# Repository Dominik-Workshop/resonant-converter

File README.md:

# Resonant Converter

## Overview

This project is an LLC resonant converter. The power supply is designed to step down a nominal 60V input to a 12V output, capable of delivering up to 10A of continuous current (120W).

The board features power telemetry using an INA219 sensor, which can be easily interfaced via a standard QWIIC connector.

### Key Features

* **Input Voltage:** 60V ± 5%
* **Output:** 12V @ 10A
* **Topology:** LLC Resonant Converter
* **Telemetry:** Onboard INA219 power monitor with a QWIIC I2C connector
* **Magnetics:** Custom-wound transformer

## Project Status

**Design:** ✅ → **Fabrication & Assembly:** ✅ → **Bring-up:** ✅

> [!IMPORTANT]
> **Hardware modification required (rev.1.0.0):**
>
> Replace `R20` with a diode (e.g. `1N4148`) to prevent VCCP from backfeeding `U3`. Without this fix, VCCP remains too low for the LLC controller `U1` to start up.

## Used Tools

* [KiCad](https://www.kicad.org/) - Schematic and PCB design

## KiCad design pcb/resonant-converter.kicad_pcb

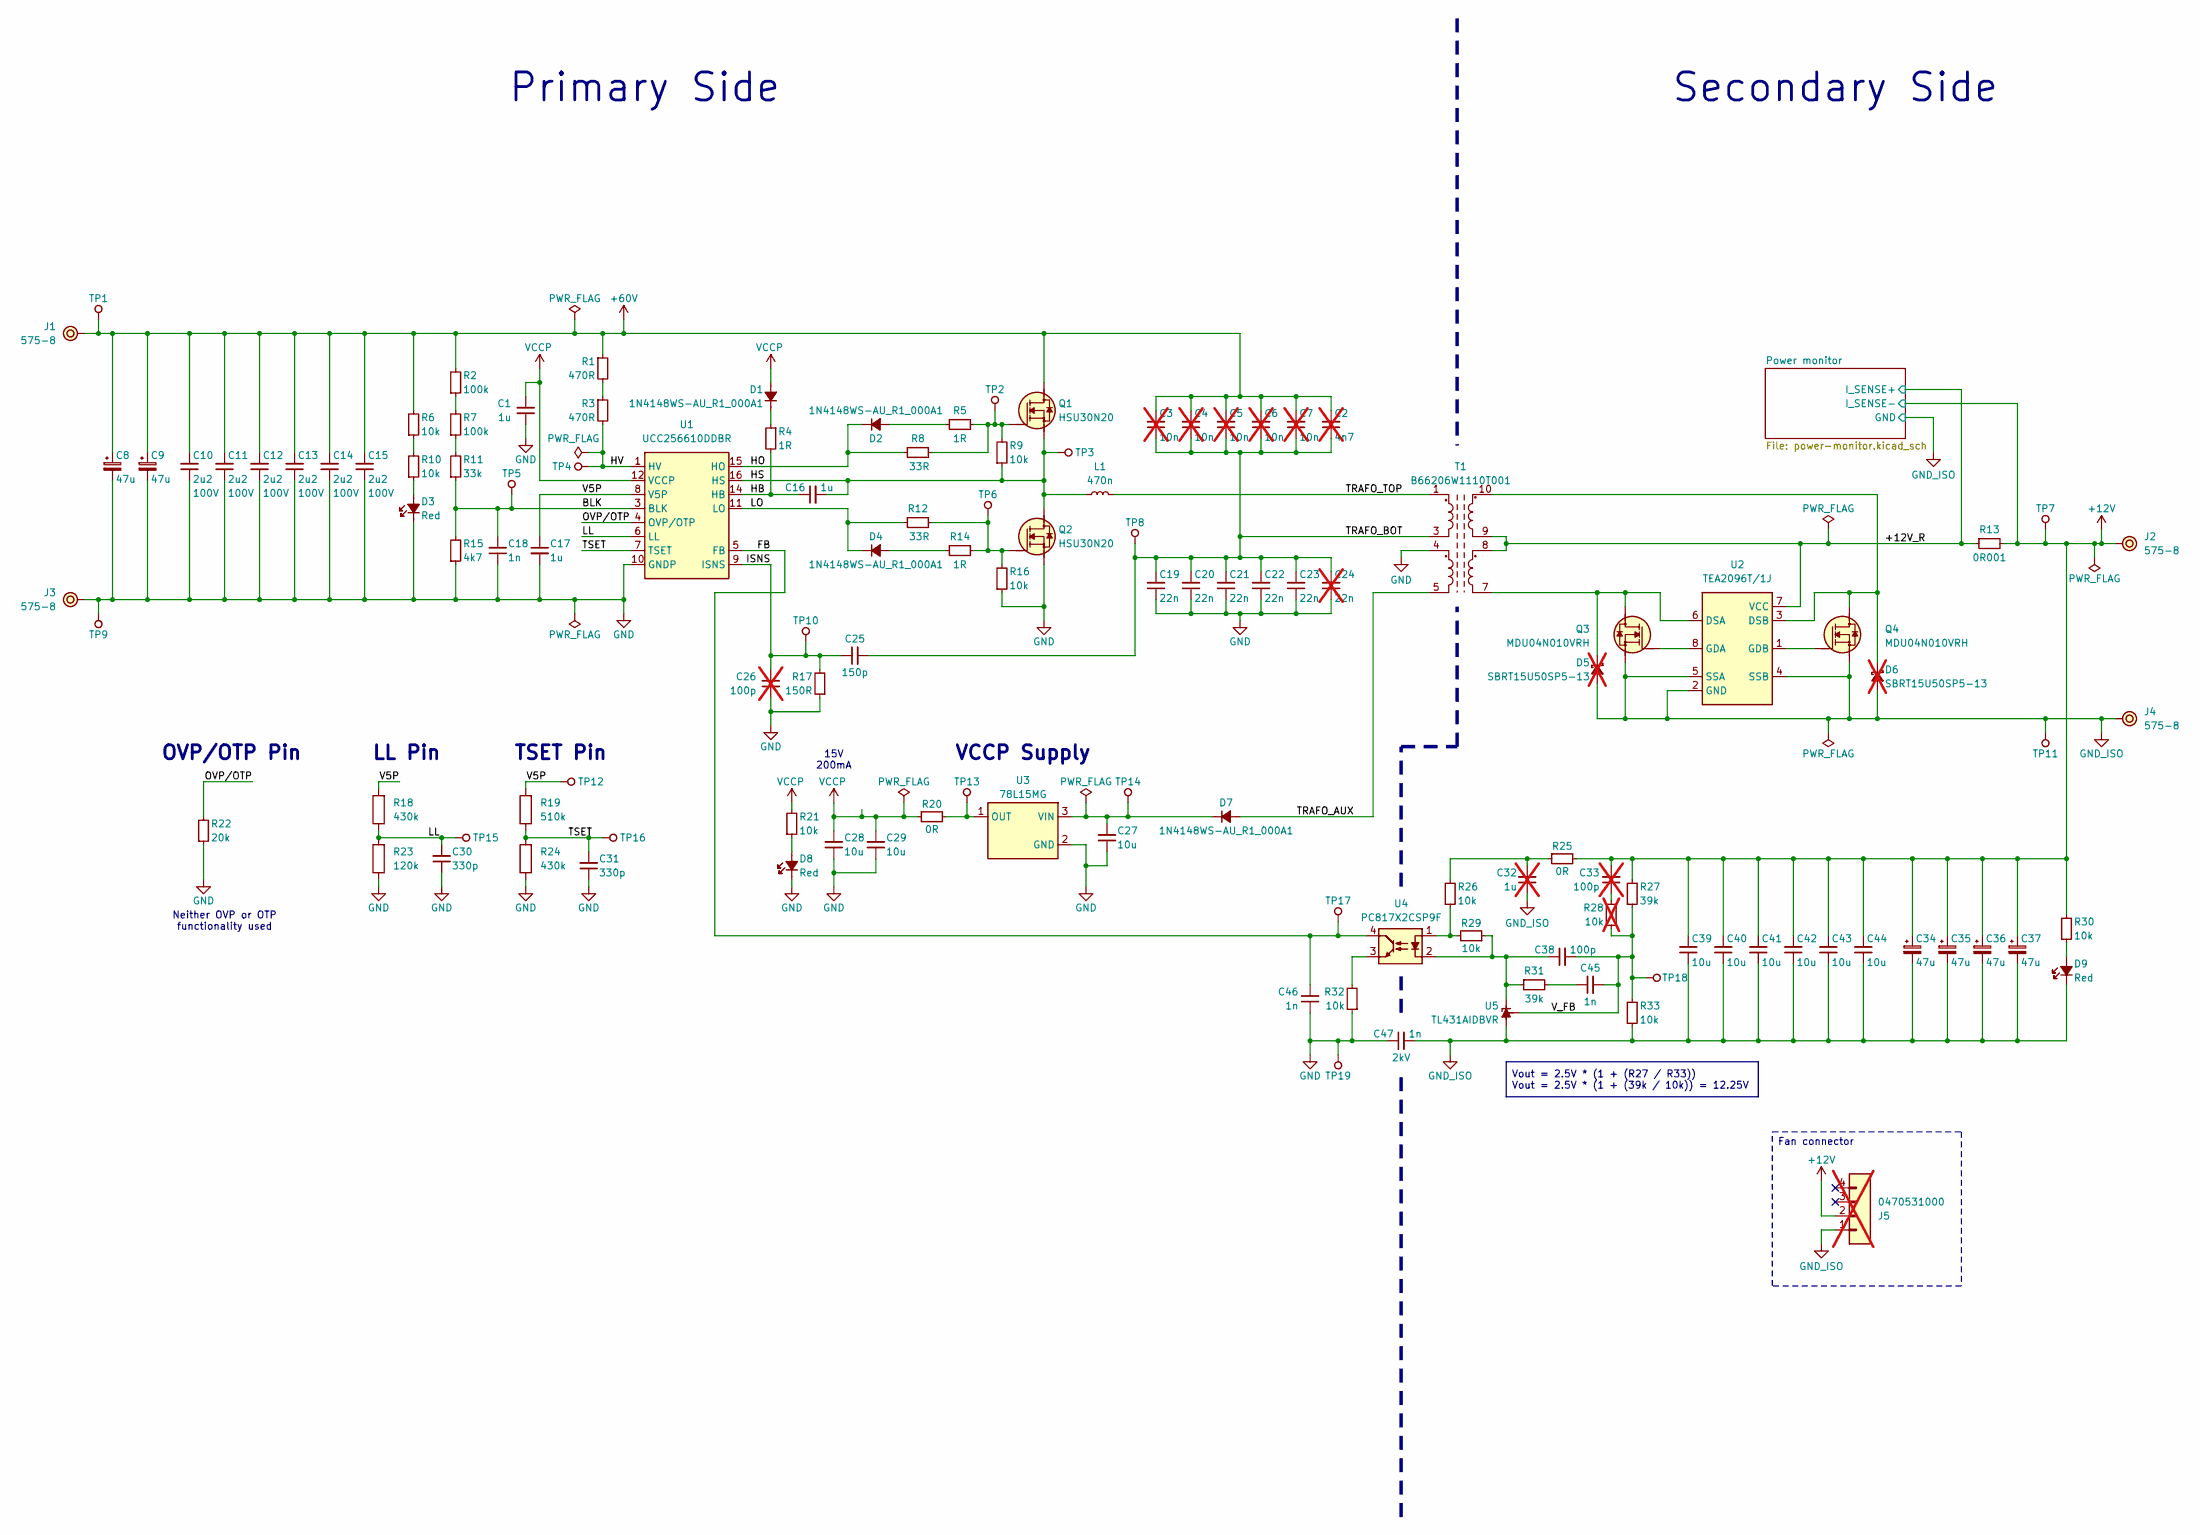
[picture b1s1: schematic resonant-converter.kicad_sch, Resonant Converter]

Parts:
C1, C16, C17: C-1u-0402; C_0402_1005Metric; Tolerance 10%; Voltage 25V; MPN CL05A105KA5NQNC; LCSC C52923
C2: C-4n7-100V-NP0-1206; C_1206_3216Metric; Tolerance 5%; Voltage 100V; MPN CC1206JRNPO0BN472; LCSC C577156; not fitted
C3, C4, C5, C6, C7: C-10n-100V-C0G-1206; C_1206_3216Metric; Tolerance 5%; Voltage 100V; MPN GCM3195C2A103JA16D; LCSC C184799; not fitted
C8, C9, C34, C35, C36, C37: C_Pol_47u_100V_D8mm_H11.5; C_Pol_D8mm_H11.5mm_P3.5mm; Tolerance 20%; Voltage 100V; MPN PA100V47M8X11; LCSC C49233039
C10, C11, C12, C13, C14, C15: C-2u2-100V-1206; C_1206_3216Metric; Tolerance 10%; Voltage 100V; MPN CL31B225KCHSNNE; LCSC C170101
C18, C45, C46: C-1n-0402; C_0402_1005Metric; Tolerance 10%; Voltage 50V; MPN 0402B102K500NT; LCSC C1523
C19, C20, C21, C22, C23: C-22n-100V-C0G-1206; C_1206_3216Metric; Tolerance 5%; Voltage 100V; MPN GRM3195C2A223JA01D; LCSC C711005
C24: C-22n-100V-C0G-1206; C_1206_3216Metric; Tolerance 5%; Voltage 100V; MPN GRM3195C2A223JA01D; LCSC C711005; not fitted
C25: C-150p-0402; C_0402_1005Metric; Tolerance 10%; Voltage 50V; MPN 0402B151K500NT; LCSC C1527
C26, C33: C-100p-0402; C_0402_1005Metric; Tolerance 5%; Voltage 50V; MPN 0402CG101J500NT; LCSC C1546; not fitted
C27, C28, C29, C39, C40, C41, C42, C43, C44: C-10u-0805; C_0805_2012Metric; Tolerance 10%; Voltage 50V; MPN GRM21BR61H106KE43L; LCSC C440198
C30, C31: C-330p-0402; C_0402_1005Metric; Tolerance 5%; Voltage 50V; MPN CL05C331JB5NNNC; LCSC C13533
C32: C-1u-0402; C_0402_1005Metric; Tolerance 10%; Voltage 25V; MPN CL05A105KA5NQNC; LCSC C52923; not fitted
C38: C-100p-0402; C_0402_1005Metric; Tolerance 5%; Voltage 50V; MPN 0402CG101J500NT; LCSC C1546
C47: C-1n-2kV-1206; C_1206_3216Metric; Tolerance 10%; Voltage 2kV; MPN 1206B102K202NT; LCSC C9196
D1, D2, D4, D7: 1N4148WS-AU; D_SOD-323F; Reverse Voltage 75V; MPN 1N4148WS-AU_R1_000A1; LCSC C2999083
D3, D8, D9: LED-R-0603_KT-0603R; LED_0603_1608Metric_R; Forward voltage 1.8V-2.4V; MPN KT-0603R; LCSC C2286
D5, D6: SBRT15U50SP5-13; PowerDI-5; Reverse Voltage 50V; MPN SBRT15U50SP5-13; LCSC C211388; not fitted
J1, J2, J3, J4: Banana_Jack_Keystone_575-8; Conn_Banana_Jack_Keystone_575-8; MPN 575-8; LCSC C4994335
J5: Molex_KK_1x4_0470531000; Conn_Molex_KK_1x4_0470531000; MPN 0470531000; LCSC C240840; not fitted
L1: L-470n-7A-dehongganying-DH0520H-R47M; L-dehongganying-DH0520H; Tolerance 20%; MPN DH0520H-R47M; LCSC C41407028
Q1, Q2: HSU30N20; TO-252-3; MPN HSU30N20; LCSC C42376812
Q3, Q4: MDU04N010VRH; PDFN-56-8; MPN MDU04N010VRH; LCSC C51891825
R1, R3: R-470R-0402; R_0402_1005Metric; Tolerance 1%; MPN 0402WGF4700TCE; LCSC C25117
R2, R7: R-100k-0402; R_0402_1005Metric; Tolerance 1%; MPN 0402WGF1003TCE; LCSC C25741
R4, R5, R14: R-1R-0603; R_0603_1608Metric; Tolerance Tolerance; MPN 0603WAF100KT5E; LCSC C22936
R6, R9, R10, R16, R21, R26, R29, R30, R32, R33: R-10k-0402; R_0402_1005Metric; Tolerance 1%; MPN 0402WGF1002TCE; LCSC C25744
R8, R12: R-33R-0402; R_0402_1005Metric; Tolerance 1%; MPN 0402WGF330JTCE; LCSC C25105
R11: R-33k-0402; R_0402_1005Metric; Tolerance 1%; MPN 0402WGF3302TCE; LCSC C25779
R13: R-0R001-1206; R_1206_3216Metric; Tolerance 5%; MPN FRM121WJR001TM; LCSC C7419993
R15: R-4k7-0402; R_0402_1005Metric; Tolerance 1%; MPN 0402WGF4701TCE; LCSC C25900
R17: R-150R-0402; R_0402_1005Metric; Tolerance 1%; MPN 0402WGF1500TCE; LCSC C25082
R18, R24: 430k; R_0402_1005Metric
R19: 510k; R_0402_1005Metric; LCSC C11616
R20, R25: R-0R-0402; R_0402_1005Metric; Tolerance 1%; MPN 0402WGF0000TCE; LCSC C17168
R22: R-20k-0402; R_0402_1005Metric; Tolerance 1%; MPN 0402WGF2002TCE; LCSC C25765
R23: 120k; R_0402_1005Metric; LCSC C25750
R27, R31: R-39k-0402; R_0402_1005Metric; Tolerance 1%; MPN 0402WGF3902TCE; LCSC C25783
R28: R-10k-0402; R_0402_1005Metric; Tolerance 1%; MPN 0402WGF1002TCE; LCSC C25744; not fitted
T1: B66206W1110T001; Bobbin_B66206W1110T001; MPN B66206W1110T001
TP1, TP2, TP3, TP4, TP5, TP6, TP7, TP8, TP9, TP10, TP11, TP12, TP13, TP14, TP15, TP16, TP17, TP18, TP19: TP_SMD_1mm
U1: UCC256610DDBR; DDB0014A; MPN UCC256610DDBR; LCSC C49247863
U2: TEA2096T/1J; SOIC-8_3.9x4.9mm_P1.27mm; MPN TEA2096T/1J; LCSC C5365715
U3: 78L15MG; SOT-223; MPN 78L15MG; LCSC C49451967
U4: PC817X2CSP9F; SMD-4_6.5x4.6mm_P2.54mm; MPN PC817X2CSP9F; LCSC C66405
U5: TL431AIDBVR; SOT-23-5; MPN TL431AIDBVR; LCSC C144392

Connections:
+12V: C33.2, C34.1, C35.1, C36.1, C37.1, C39.2, C40.2, C41.2, C42.2, C43.2, C44.2, J2.1, J5.2, R13.2, R25.2, R27.2, R30.2, TP7.1; also elsewhere on the board
+60V: C2.2, C3.2, C4.2, C5.2, C6.2, C7.2, C8.1, C9.1, C10.2, C11.2, C12.2, C13.2, C14.2, C15.2, J1.1, Q1.3 (D), R1.1, R2.2, R6.2, TP1.1
/+12V_R: R13.1, T1.8, T1.9, U2.7 (VCC); also elsewhere on the board
/BLK: C18.2, R11.1, R15.2, TP5.1, U1.3 (BLK)
/FB: C46.2, TP17.1, U1.5 (FB), U4.4
/HB: C16.1, R4.2, U1.14 (HB)
/HO: D2.1 (C), R8.1, U1.15 (HO)
/HS: C16.2, L1.1, Q1.2 (S), Q2.3 (D), R9.1, TP3.1, U1.16 (HS)
/HV: R3.2, TP4.1, U1.1 (HV)
/ISNS: C25.1, C26.2, R17.2, TP10.1, U1.9 (ISNS)
/LL: C30.2, R18.1, R23.2, TP15.1, U1.6 (LL)
/LO: D4.1 (C), R12.1, U1.11 (LO)
/OVP/OTP: R22.2, U1.4 (OVP/OTP)
/TRAFO_AUX: D7.2 (A), T1.5
/TRAFO_BOT: C2.1, C3.1, C4.1, C5.1, C6.1, C7.1, C19.2, C20.2, C21.2, C22.2, C23.2, C24.2, C25.2, T1.3, TP8.1
/TRAFO_TOP: L1.2, T1.1
/TSET: C31.2, R19.1, R24.2, TP16.1, U1.7 (TSET)
/V5P: C17.1, R18.2, R19.2, TP12.1, U1.8 (V5P)
/V_FB: C38.2, C45.2, R27.1, R28.1, R33.2, TP18.1, U5.4 (REF)
GND: C1.1, C8.2, C9.2, C10.1, C11.1, C12.1, C13.1, C14.1, C15.1, C17.2, C18.1, C19.1, C20.1, C21.1, C22.1, C23.1, C24.1, C26.1, C27.1, C28.1, C29.1, C30.1, C31.1, C46.1, C47.1, D3.1 (C), D8.1 (C), J3.1, Q2.2 (S), R15.1, R16.1, R17.1, R22.1, R23.1, R24.1, R32.1, T1.4, TP9.1, TP19.1, U1.10 (GNDP), U3.2 (GND), U3.4 (GND)
GND_ISO: C32.1, C34.2, C35.2, C36.2, C37.2, C39.1, C40.1, C41.1, C42.1, C43.1, C44.1, C47.2, D5.2 (A), D6.2 (A), D9.1 (C), J4.1, J5.1, Q3.1 (S), Q3.2 (S), Q3.3 (S), Q4.1 (S), Q4.2 (S), Q4.3 (S), R33.1, TP11.1, U2.2 (GND), U2.4 (SSB), U2.5 (SSA), U5.5 (A); also elsewhere on the board
unnamed: C32.2, R25.1, R26.2
unnamed: C33.1, R28.2
unnamed: C45.1, R31.2
unnamed: D1.1 (C), R4.1
unnamed: D2.2 (A), R5.1
unnamed: D3.2 (A), R10.1
unnamed: D4.2 (A), R14.1
unnamed: D5.1 (C), Q3.5 (D), T1.7, U2.6 (DSA)
unnamed: D6.1 (C), Q4.5 (D), T1.10, U2.3 (DSB)
unnamed: C27.2, D7.1 (C), TP14.1, U3.3 (VIN)
unnamed: D8.2 (A), R21.1
unnamed: D9.2 (A), R30.1
unnamed: Q1.1 (G), R5.2, R8.2, R9.2, TP2.1
unnamed: Q2.1 (G), R12.2, R14.2, R16.2, TP6.1
unnamed: Q3.4 (G), U2.8 (GDA)
unnamed: Q4.4 (G), U2.1 (GDB)
unnamed: R1.2, R3.1
unnamed: R2.1, R7.2
unnamed: R6.1, R10.2
unnamed: R7.1, R11.2
unnamed: R26.1, R29.2, U4.1
unnamed: R32.2, U4.3
unnamed: R20.2, TP13.1, U3.1 (OUT)
unnamed: C38.1, R29.1, R31.1, U4.2, U5.3 (K)
VCCP: C1.2, C28.2, C29.2, D1.2 (A), R20.1, R21.2, U1.12 (VCCP)

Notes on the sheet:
Secondary Side
VCCP Supply
TSET Pin
OVP/OTP Pin
LL Pin
Neither OVP or OTP functionality used
Primary Side
15V 200mA
Fan connector
Vout = 2.5V * (1 + (R27 / R33)) Vout = 2.5V * (1 + (39k / 10k)) = 12.25V

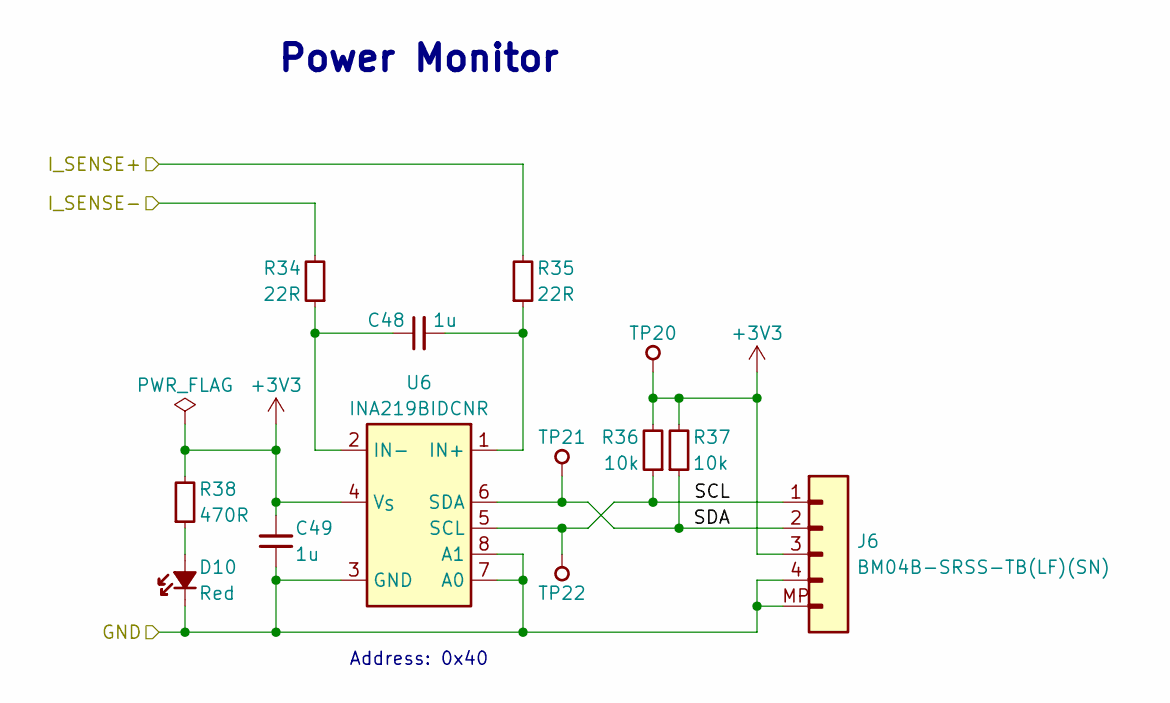
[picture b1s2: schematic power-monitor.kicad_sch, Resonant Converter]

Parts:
C48, C49: C-1u-0402; C_0402_1005Metric; Tolerance 10%; Voltage 25V; MPN CL05A105KA5NQNC; LCSC C52923
D10: LED-R-0603_KT-0603R; LED_0603_1608Metric_R; Forward voltage 1.8V-2.4V; MPN KT-0603R; LCSC C2286
J6: JST_SH_1x4_BM04B-SRSS-TB-LF-SN; Conn_JST_SH_1x4_BM04B-SRSS-TB; MPN BM04B-SRSS-TB(LF)(SN); LCSC C160390
R34, R35: R-22R-0402; R_0402_1005Metric; Tolerance 1%; MPN 0402WGF220JTCE; LCSC C25092
R36, R37: R-10k-0402; R_0402_1005Metric; Tolerance 1%; MPN 0402WGF1002TCE; LCSC C25744
R38: R-470R-0402; R_0402_1005Metric; Tolerance 1%; MPN 0402WGF4700TCE; LCSC C25117
TP20, TP21, TP22: TP_SMD_1mm
U6: INA219BIDCNR; SOT-23-8; MPN INA219BIDCNR; LCSC C962069

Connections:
+3V3: C49.2, J6.3, R36.2, R37.2, R38.2, TP20.1, U6.4 (V_{S})
+12V: R34.2; also elsewhere on the board
/+12V_R: R35.2; also elsewhere on the board
/Power monitor/SCL: J6.1, R36.1, TP22.1, U6.5 (SCL)
/Power monitor/SDA: J6.2, R37.1, TP21.1, U6.6 (SDA)
GND_ISO: C49.1, D10.1 (C), J6.4, J6.MP, U6.3 (GND), U6.7 (A0), U6.8 (A1); also elsewhere on the board
unnamed: D10.2 (A), R38.1
unnamed: C48.2, R35.1, U6.1 (IN+)
unnamed: C48.1, R34.1, U6.2 (IN-)

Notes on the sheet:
Address: 0x40
Power Monitor

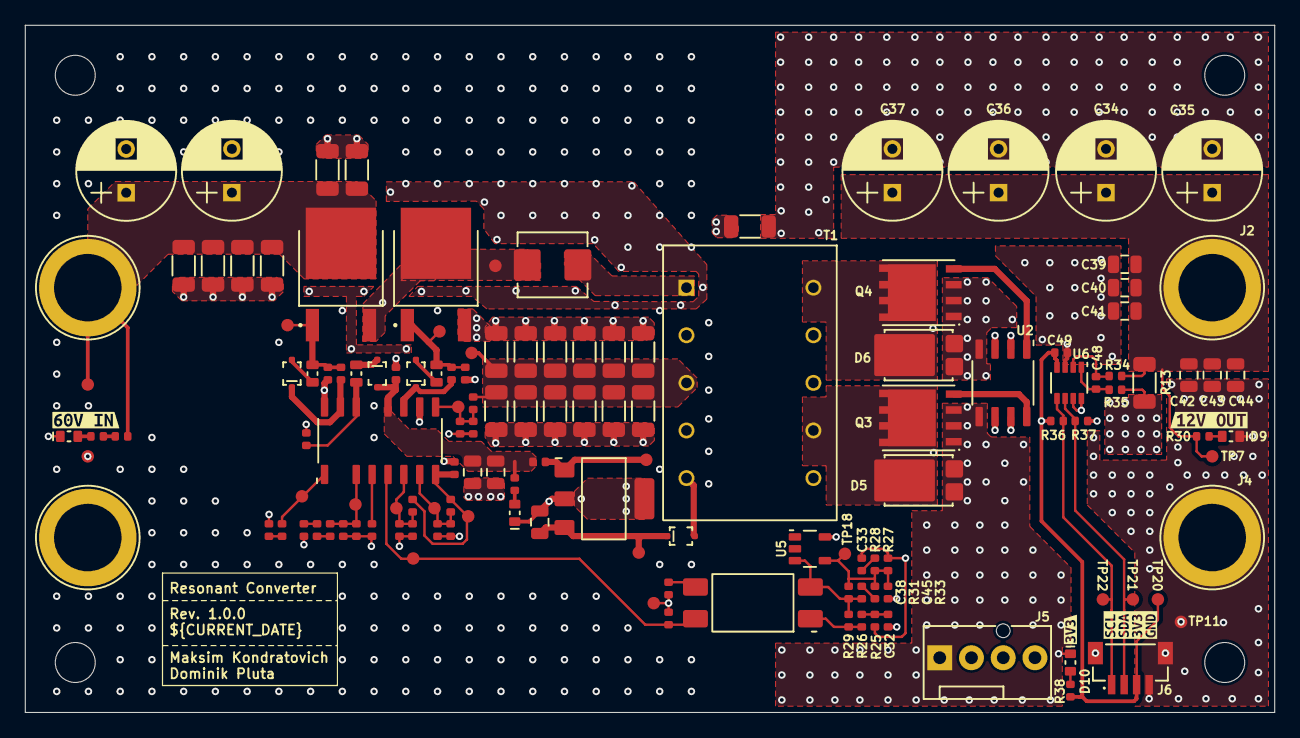
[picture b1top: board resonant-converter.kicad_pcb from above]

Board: 4 copper layers, 100.0 x 55.0 mm, 141 parts (0 on the bottom side), 52 nets.

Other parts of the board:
kibuzzard-69F4E13D: G***; kibuzzard-69F4E13D
kibuzzard-69F4E155: G***; kibuzzard-69F4E155
kibuzzard-69F52FAE: G***; kibuzzard-69F52FAE
kibuzzard-69F53099: G***; kibuzzard-69F53099

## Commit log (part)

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2026-03-23 Initialize PCB project
2026-03-25 PCB: Setup PCB stackup, DRC and pre-defined sizes
2026-03-26 WIP: Create PCB mockup
2026-03-26 Add WIP note in README
2026-03-28 Add LLC controller IC
2026-03-28 Add output rectifier schottky diodes
2026-04-01 Add synchronous rectifier
2026-04-07 Add resonant inductor and capacitors
2026-04-12 [#4] Sch: Add INA219 power monitor
2026-04-12 PCB: Update PCB from schematic, add transformer core
2026-04-12 [#4] Sch: Add transformer, draft feedback circuitry
2026-04-13 [#4] Sch: Move INA219 power monitor to separate sheet, select initial feedback components values
2026-04-15 [#3] Add input capacitors and power indicator LED, change GND names on primary and secondary
2026-04-18 [#4] Sch: Change rectifier MOSFETS
2026-04-18 [#4] Sch: Add input and output capacitors, pri-sec interference capacitor and QWIIC connector, refactor schematic
2026-04-18 [#3] Sch: Change primary side MOSFETS
2026-04-20 [#4] Sch: Adjust feedback network component values, add optional compensation components
2026-04-20 [#4] Sch: Add I2C pullups, write down INA219's address, add hierarchical label for power monitor's GND
2026-04-20 [#4] Sch: Add optional fan connector
2026-04-20 [#4] Sch: Fill out title block in power monitor sheet
2026-04-22 [#3] Complete primary side schematic
2026-04-22 Sch: Replace symbols with ones from library
2026-04-22 Sch: Add 15V LDO for VCCP
2026-04-22 Update PCB from schematic, add project info block on silkscreen
2026-04-22 WIP: Sch: Improve readability
2026-04-22 Sch: Improve readability
2026-04-22 Sch: Change output capacitors from 0603 to 0805
2026-04-22 Sch: Decrease spacing between resonant capacitors
2026-04-22 Re-annotate schematic, update PCB from schematic
2026-04-22 Sch: Add 0R and 0402 1uF to VCCP line
2026-04-22 Sch: Add test points and 3V3 power indicator LED
2026-04-22 Sch: Re-annotate schematic, clear ERC
2026-04-22 PCB: Update PCB from schematic, layout power monitor section
2026-04-22 PCB: Perform initial component placement
2026-04-22 README: Add badges and temporary PCB render
2026-04-22 Add LICENSE
2026-04-25 Add mounting holes, fix 4n7 capacitor size
2026-05-01 Completed primary side PCB layout
2026-05-01 WIP: Layout PCB secondary side
2026-05-01 PCB: Layout the rectifier
2026-05-02 PCB: Layout most of the secondary side
2026-05-02 PCB: Layout all secondary side connections
2026-05-02 PCB: Align PCB to bigger grid, arrange component designators, add via stitching on secondary side
2026-05-02 PCB: Clear DRC
2026-05-02 Update PCB render
2026-05-02 Added via stitching to the primary side
2026-05-04 Move PCB SHA, update date
2026-05-04 Remove WIP note from README
2026-05-27 Add project description in README
